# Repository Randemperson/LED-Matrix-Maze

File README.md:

# LED Matrix Maze – Custom PCB Project

- **Tools:** KiCad, Raspberry Pi, MAX7219, Thonny IDE and VSCode
- **Focus:** PCB Design, Embedded Systems, Interactive Hardware

## Overview
This project implements an interactive LED matrix maze system using a custom
PCB designed in KiCad. The board integrates an LED driver, microcontroller
interface, and user inputs, and is designed for makerspace prototyping and
iteration.

## Prototyping
Before PCB design, the circuit was validated using a breadboard prototype
to test LED matrix control, button inputs, and maze logic. This prototype was
used to verify functionality prior to committing to fabricating the PCB.

## Fabrication Plan
The PCB is designed for rapid prototyping using professional PCB milling and
laser equipment available through the GT Hive makerspace. The design is prepared
for fabrication on an LPKF ProtoMat S103 and ProtoLaser U4 system, enabling fast
iteration and testing prior to final assembly.

## What I Did
- Integrated a MAX7219 LED driver with a Raspberry Pi Pico via SPI, including
  button input circuitry for user interaction
- Designed schematics and PCB layout in KiCAD with userfriendlyness and functionality in mind
- Implemented recursive backtracking maze generation algorithm

## Key Challenges
- Addressed signal integrity issues in SPI communication through impedance matching
- Designed custom multiplexing logic to work within MAX7219's binary (on/off) output limitation for monochrome LED control

## Repository Structure
- `/renders` – 3D PCB renders
- `/photos` – Assembled board photos
- `/schematic` – Schematics
- `/pcb` – PCB layout files
- `/code` – Firmware and control logic

## Status
Design complete and ready for fabrication in January when spring semester starts.

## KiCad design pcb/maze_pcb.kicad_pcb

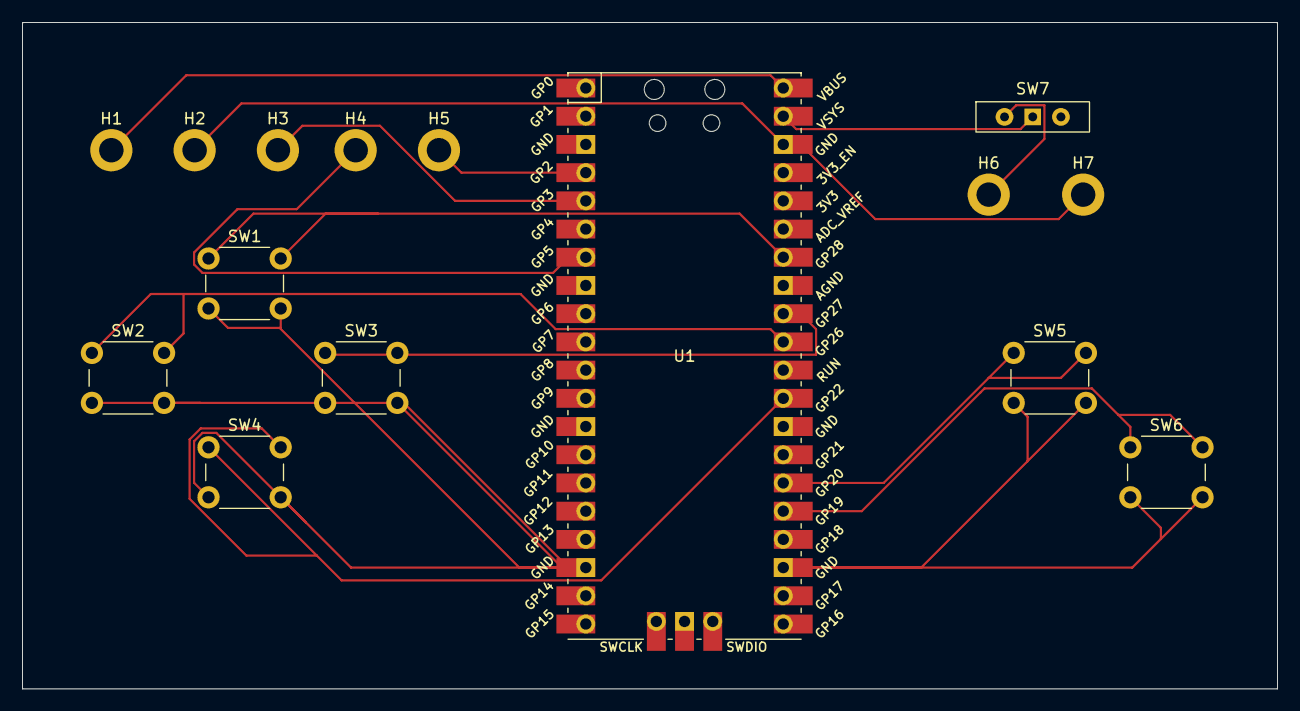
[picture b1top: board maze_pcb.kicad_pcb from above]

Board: 2 copper layers, 113.0 x 60.0 mm, 15 parts (0 on the bottom side), 15 nets.

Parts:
H1, H2, H3, H4, H5, H6, H7: MountingHole_Pad; MountingHole_2.2mm_M2_DIN965_Pad
SW1, SW2, SW3, SW4, SW5, SW6: SW_Push; SW_PUSH_6mm
SW7: SW_SPDT; SW_Slide-03_Wuerth-WS-SLTV_10x2.5x6.4_P2.54mm
U1: Pico; RPi_Pico_SMD_TH

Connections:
unnamed: H2.1, H7.1, U1.38 (GND)
unnamed: SW1.2, SW2.2, SW3.2, SW4.2, U1.18 (GND)
unnamed: SW5.2, SW6.2, U1.23 (GND)
unnamed: SW7.1 (A), U1.39 (VSYS)
unnamed: H6.1, SW7.2 (B)
unnamed: H5.1, U1.4 (GPIO2)
unnamed: H3.1, U1.5 (GPIO3)
unnamed: H4.1, U1.7 (GPIO5)
unnamed: SW6.1, U1.25 (GPIO19)
unnamed: SW5.1, U1.26 (GPIO20)
unnamed: SW4.1, U1.29 (GPIO22)
unnamed: SW2.1, U1.31 (GPIO26_ADC0)
unnamed: SW3.1, U1.32 (GPIO27_ADC1)
unnamed: SW1.1, U1.34 (GPIO28_ADC2)
unnamed: H1.1, U1.40 (VBUS)

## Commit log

2025-10-31 added game
2025-11-15 Add Improved Maze formula
2025-12-29 Add README
    Added project overview, prototyping details, fabrication plan, and repository structure.
2025-12-29 Add README
    Added detailed project overview, prototyping information, fabrication plan, and challenges faced during development.
2025-12-29 Create renders folder
2025-12-29 Create photos folder
2025-12-29 Create schematic folder
2025-12-29 Create pcb folder
2025-12-29 Reorganize code into src directory
2025-12-29 Add renders
2025-12-29 Rename isometric render.png to isometric_render.png
2025-12-29 Rename top render.png to top_render.png
2025-12-29 Add PCB files
2025-12-29 Added schematic
2025-12-29 update main.py code
2025-12-29 Add breadboard prototype image
2025-12-29 Add breadboard photo
2025-12-29 Update README
    Updated terminology from 'fabrication' to 'design' for clarity.
